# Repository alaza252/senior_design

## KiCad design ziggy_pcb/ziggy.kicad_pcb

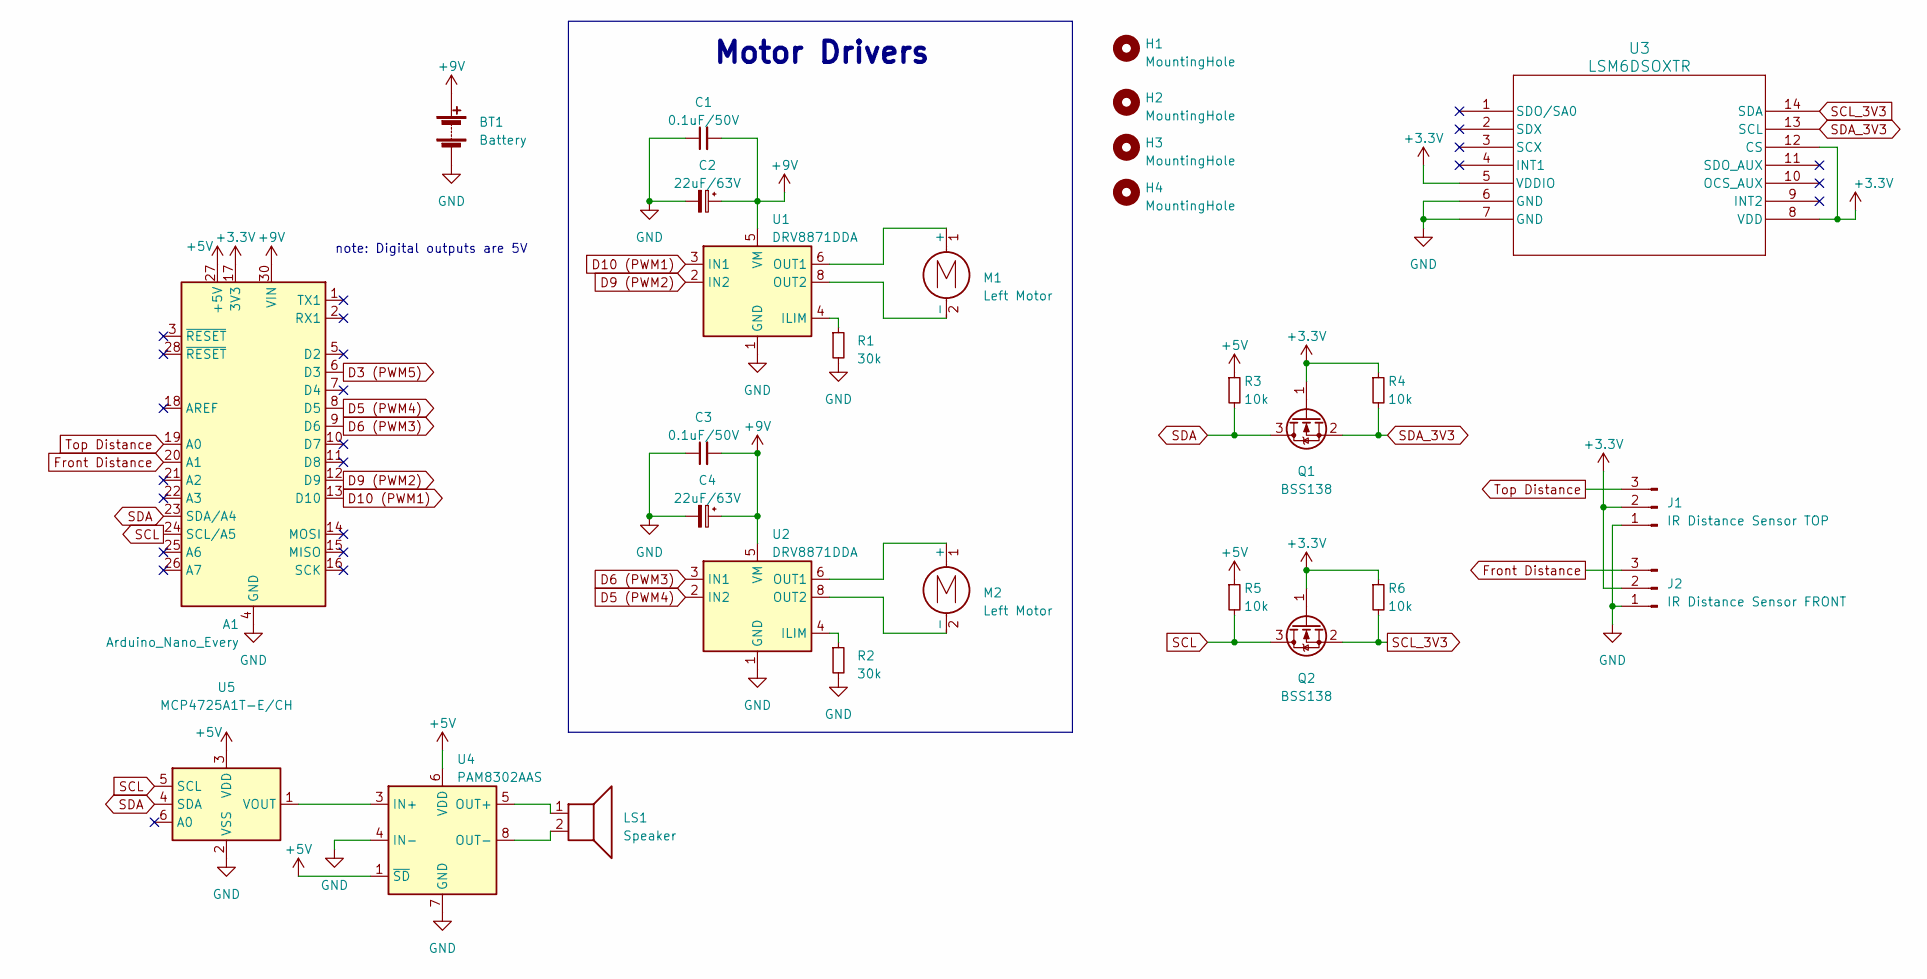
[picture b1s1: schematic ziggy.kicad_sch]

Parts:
A1: Arduino_Nano_Every; Arduino_Nano
BT1: Battery; SolderWire-1sqmm_1x02_P5.4mm_D1.4mm_OD2.7mm_Relief
C1, C3: 0.1uF/50V; C_0402_1005Metric
C2, C4: 22uF/63V; CP_Elec_6.3x9.9
H1, H2, H3, H4: MountingHole; MountingHole_3.2mm_M3
J1: IR Distance Sensor TOP; JST_SUR_BM03B-SURS-TF_1x03-1MP_P0.80mm_Vertical
J2: IR Distance Sensor FRONT; JST_SUR_SM03B-SURS-TF_1x03-1MP_P0.80mm_Horizontal
LS1: Speaker; JST_SUR_SM03B-SURS-TF_1x03-1MP_P0.80mm_Horizontal
M1, M2: Left Motor; SolderWire-0.1sqmm_1x02_P3.6mm_D0.4mm_OD1mm
Q1, Q2: BSS138; SOT-23
R1, R2: 30k; R_0402_1005Metric
R3, R4, R5, R6: 10k; R_0402_1005Metric
U1, U2: DRV8871DDA; Texas_HTSOP-8-1EP_3.9x4.9mm_P1.27mm_EP2.95x4.9mm_Mask2.4x3.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
U3: LSM6DSOXTR; LGA-14L_STM
U4: PAM8302AAS; MSOP-8_3x3mm_P0.65mm
U5: MCP4725A1T-E/CH; SOT-23-6

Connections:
+3.3V: A1.17 (3V3), J1.2, J2.2, Q1.1 (G), Q2.1 (G), R4.1, R6.1, U3.5 (VDDIO), U3.8 (VDD), U3.12 (CS)
+5V: A1.27 (+5V), R3.1, R5.1, U4.1 (~SD), U4.6 (VDD), U5.3 (VDD)
+9V: A1.30 (VIN), BT1.1 (+), C1.2, C2.1, C3.2, C4.1, U1.5 (VM), U2.5 (VM)
D3 (PWM5): A1.6 (D3)
D5 (PWM4): A1.8 (D5), U2.2 (IN2)
D6 (PWM3): A1.9 (D6), U2.3 (IN1)
D9 (PWM2): A1.12 (D9), U1.2 (IN2)
D10 (PWM1): A1.13 (D10), U1.3 (IN1)
Front Distance: A1.20 (A1), J2.3
GND: A1.4 (GND), A1.29 (GND), BT1.2 (-), C1.1, C2.2, C3.1, C4.2, J1.1, J2.1, R1.2, R2.2, U1.1 (GND), U1.7 (GND), U1.9 (GND), U2.1 (GND), U2.7 (GND), U2.9 (GND), U3.6 (GND), U3.7 (GND), U4.4 (IN-), U4.7 (GND), U5.2 (VSS)
unnamed: M1.1 (+), U1.6 (OUT1)
unnamed: M1.2 (-), U1.8 (OUT2)
unnamed: M2.1 (+), U2.6 (OUT1)
unnamed: M2.2 (-), U2.8 (OUT2)
unnamed: R1.1, U1.4 (ILIM)
unnamed: R2.1, U2.4 (ILIM)
unnamed: U4.3 (IN+), U5.1 (VOUT)
unnamed: LS1.1, U4.5 (OUT+)
unnamed: LS1.2, U4.8 (OUT-)
SCL: A1.24 (SCL/A5), Q2.3 (D), R5.2, U5.5 (SCL)
SCL_3V3: Q2.2 (S), R6.2, U3.14 (SDA)
SDA: A1.23 (SDA/A4), Q1.3 (D), R3.2, U5.4 (SDA)
SDA_3V3: Q1.2 (S), R4.2, U3.13 (SCL)
Top Distance: A1.19 (A0), J1.3

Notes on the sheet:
Motor Drivers
note: Digital outputs are 5V

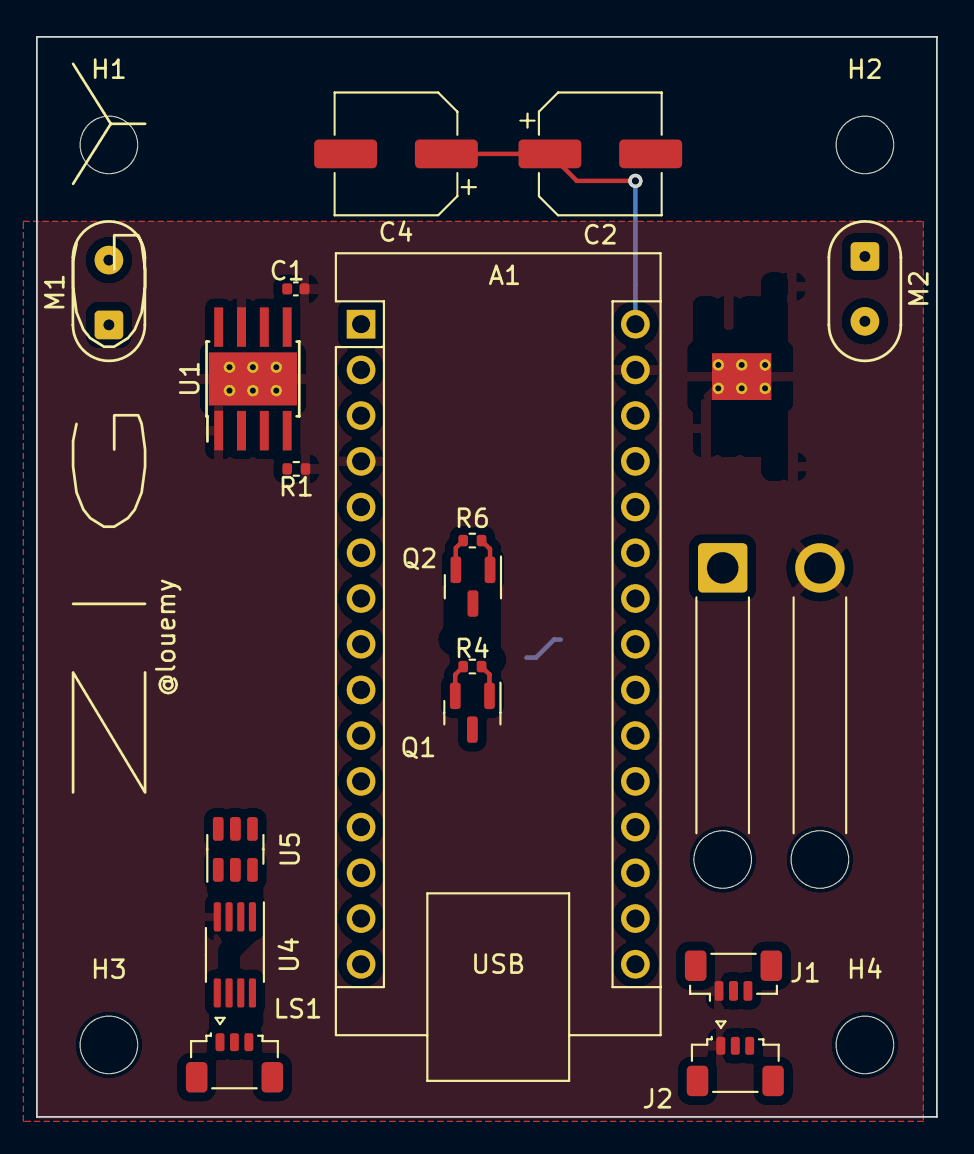
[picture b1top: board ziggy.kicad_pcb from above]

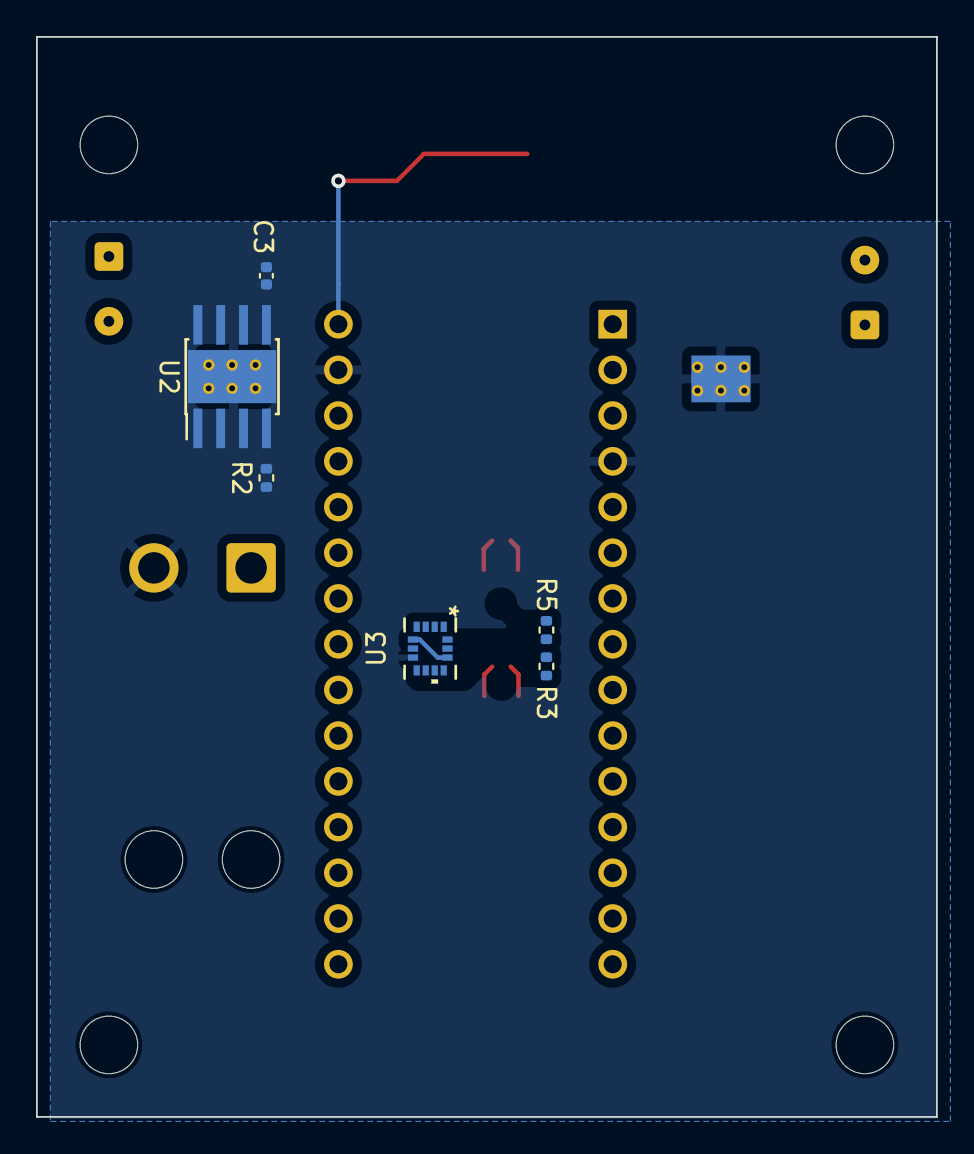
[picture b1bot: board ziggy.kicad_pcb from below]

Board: 2 copper layers, 50.0 x 60.0 mm, 28 parts (6 on the bottom side), 23 nets.

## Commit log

2023-04-08 motor test works
2023-04-24 movement tests complete
2023-08-28 end of spring 23
2023-08-31 adding pcb to repo
2023-10-25 mouse runs, sensors work as intened; need to implement sensors with microcontroller
